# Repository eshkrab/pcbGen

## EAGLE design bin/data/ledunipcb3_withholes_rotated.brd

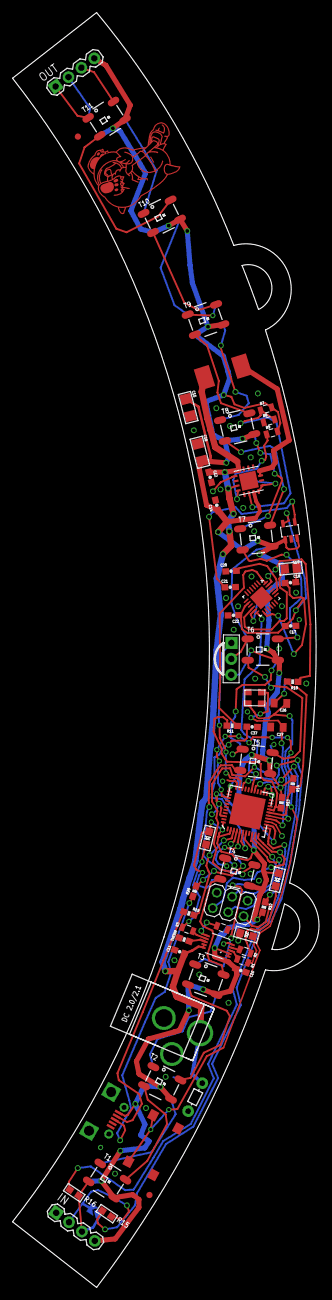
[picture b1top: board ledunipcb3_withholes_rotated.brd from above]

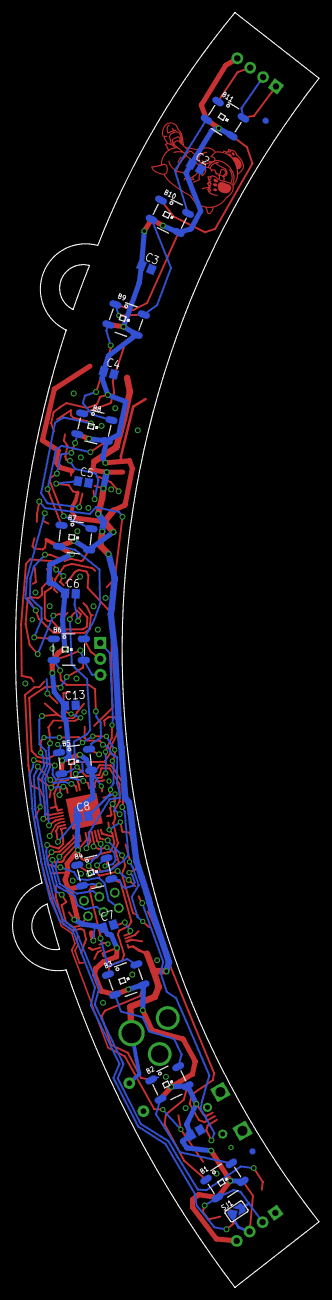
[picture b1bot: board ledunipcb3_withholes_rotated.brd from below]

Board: 2 copper layers, 48.8 x 203.2 mm, 87 parts (23 on the bottom side), 62 nets.

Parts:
B1, B2, B3, B4, B5, B6, B7, B8, B9, B10, B11: WS2812B
C1: AXIAL-5MM
C2, C3, C4, C5, C6, C7, C8, C9, C13: C0805
C10, C11, C37: 1uF; 0603-CAP
C12: 0603-CAP
C14, C22: 2.2uF; 0603-CAP
C15, C16: 100uF; 1206
C17, C21: 10nF; 0603-CAP
C18: .01uF; 0603-CAP
C19: 0.1uF; 0805
C20: 2200pF; 0603-CAP
C26, C27: 22pF; C0805K
CN1: DCJACK_2MM_PTH
CN3: MiniB USB; ZX62D-B-5PA8
IN: 1X04
JP4: ICSP; 2X03
LED10, LED12, LED14: CHIPLED_0805
LP2985-33DBVR: LP2985AIM5-3.3; SOT25
OUT: 1X04
R1, R2, R3: 470; 0805
R4: 1k; 0805
R7, R8, R9: 0805
R10, R11, R12: 10k; 0603-RES
R13, R14: 0603-RES
R15, R16: 0603
R19, R20: 22; 0603-RES
SJ1: SOLDERJUMPER_ARROW_NOPASTE
T1, T2, T3, T4, T5, T6, T7, T8, T9, T10, T11: WS2812B
THERM: 10k; 0603-RES
TPS61030: TPS61030; QFN16-4X4
U1: MPU-6000QFN-24; QFN-24-TESTING
U3: MCP73833; MSOP-10
U$1: ATMEGA32U4QFN; SPARKFUN-DIGITALIC_QFN-44
U$2: SRP7030-6R8M
U$3, U$5, U$7, U$8: FIDUCIAL; FIDUCIAL_1MM
U$4: PNA460XM
U$6: UNIMONSTER
U$9: MC32882
Y2: 16MHz KX-7; CRYSTAL-3.2-2.5

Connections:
3V3: C17.2, C18.2, C22.1, LP2985-33DBVR.5, U1.8, U1.13
5V: B1.3, B2.3, B3.3, B4.3, B5.3, B6.3, B7.3, B8.3, B9.3, B10.3, B11.3, C2.1, C3.1, C4.1, C5.1, C6.1, C7.1, C8.1, C9.1, C10.1, C13.1, C14.1, C15.1, C16.1, CN3.1, IN.4, LED10.A, LED12.A, LED14.A, LP2985-33DBVR.1, LP2985-33DBVR.3, OUT.4, R7.2, R9.2, R12.2, R13.2, R14.2, T1.3, T2.3, T3.3, T4.3, T5.3, T6.3, T7.3, T8.3, T9.3, T10.3, T11.3, TPS61030.VOUT, TPS61030.VOUT2, TPS61030.VOUT3, U3.1, U3.2, U$1.2, U$1.7, U$1.14, U$1.24, U$1.34, U$1.44, U$4.3
BUTTON: U$1.36, U$9.P$3, U$9.P$4
BYPASS: C21.1, LP2985-33DBVR.4
DATA_IN1: R16.1, U$1.27
DATA_IN1B: R15.1, U$1.31
DATA_IN1B_A: B1.2, IN.2, R15.2, SJ1.2
DATA_IN1_A: IN.3, R16.2, SJ1.1, T1.2
DATA_OUT1: T1.4, T2.2
DATA_OUT1B: B1.4, B2.2
DATA_OUT2: T2.4, T3.2
DATA_OUT2B: B2.4, B3.2
DATA_OUT3: T3.4, T4.2
DATA_OUT3B: B3.4, B4.2
DATA_OUT4: T4.4, T5.2
DATA_OUT4B: B4.4, B5.2
DATA_OUT5: T5.4, T6.2
DATA_OUT5B: B5.4, B6.2
DATA_OUT6: T6.4, T7.2
DATA_OUT6B: B6.4, B7.2
DATA_OUT7: T7.4, T8.2
DATA_OUT7B: B7.4, B8.2
DATA_OUT8: T8.4, T9.2
DATA_OUT8B: B8.4, B9.2
DATA_OUT9: T9.4, T10.2
DATA_OUT9B: B9.4, B10.2
DATA_OUT10: T10.4, T11.2
DATA_OUT10B: B10.4, B11.2
DATA_OUT11: OUT.3, T11.4
DATA_OUT11B: B11.4, OUT.2
GND: B1.1, B2.1, B3.1, B4.1, B5.1, B6.1, B7.1, B8.1, B9.1, B10.1, B11.1, C1.P$2, C2.2, C3.2, C4.2, C5.2, C6.2, C7.2, C8.2, C9.2, C10.2, C11.1, C12.2, C13.2, C14.2, C15.2, C16.2, C17.1, C18.1, C19.2, C20.2, C21.2, C22.2, C26.2, C27.2, C37.1, CN1.GND, CN3.5, IN.1, JP4.6, LP2985-33DBVR.2, OUT.1, R4.2, R8.1, T1.1, T2.1, T3.1, T4.1, T5.1, T6.1, T7.1, T8.1, T9.1, T10.1, T11.1, THERM.1, TPS61030.GND, TPS61030.LBI, TPS61030.PGND, TPS61030.PGND2, TPS61030.PGND3, TPS61030.SYNC, U1.1, U1.11, U1.18, U3.5, U$1.5, U$1.15, U$1.33, U$1.42, U$4.2, U$9.P$1, U$9.P$2, Y2.2, Y2.4
INT: U1.12, U$1.28
IR_SENS: U$1.32, U$4.1
LOWBATOUT: R9.1, TPS61030.LBO
MISO: JP4.1, U$1.11
MOSI: JP4.4, U$1.10
unnamed: LED12.C, R2.1
unnamed: R1.2, U3.3
unnamed: R2.2, U3.4
unnamed: R3.2, U3.7
unnamed: R7.1, R8.2, TPS61030.FB
unnamed: R10.1, U1.23
unnamed: R11.1, U1.24
unnamed: R20.2, U$1.4
unnamed: TPS61030.SW, TPS61030.SW2, U$2.P$2
unnamed: LED10.C, R1.1
unnamed: LED14.C, R3.1
unnamed: THERM.2, U3.8
unnamed: R4.1, U3.6
unnamed: C19.1, U1.10
unnamed: C20.1, U1.20
unnamed: CN3.2, R19.1
unnamed: CN3.3, R20.1
unnamed: R19.2, U$1.3
unnamed: C37.2, U$1.6
RST: JP4.5, R12.1, U$1.13
SCK: JP4.3, U$1.9
SCL: R10.2, R14.1, U$1.18
SDA: R11.2, R13.1, U$1.19
VBAT: C1.P$1, C11.2, C12.1, CN1.PWR, TPS61030.EN, TPS61030.VBAT, U3.9, U3.10, U$2.P$1
XTAL3: C26.1, U$1.17, Y2.3
XTAL4: C27.1, U$1.16, Y2.1

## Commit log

2015-02-23 CAN GENERATE EAGLE FILES, MOFOS
2015-03-02 generating correct number of 'parts'
2015-03-02 started on instances
2015-04-17 i don't remember, it's been two months
2015-04-17 working on 'writeInst', BUG in GUI - values aren't saved

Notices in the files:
parts and their libraries:
SparkFun-Connectors: Licensing: CC v3.0 Share-Alike You are welcome to use this library for commercial purposes.
microbuilder: This work is placed in the public domain, and may be freely used for commercial and non-commercial work with the following conditions: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
